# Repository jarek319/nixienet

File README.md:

# nixienet
Connecting 1960's tube tech to 2010's Wifi chips!

This Wifi gadget connects to time and weather forecast servers and uses Nixie tubes to display the current time and upcoming weather.

It's one of the most full designs I've ever made, from insides to outsides. So fun :)

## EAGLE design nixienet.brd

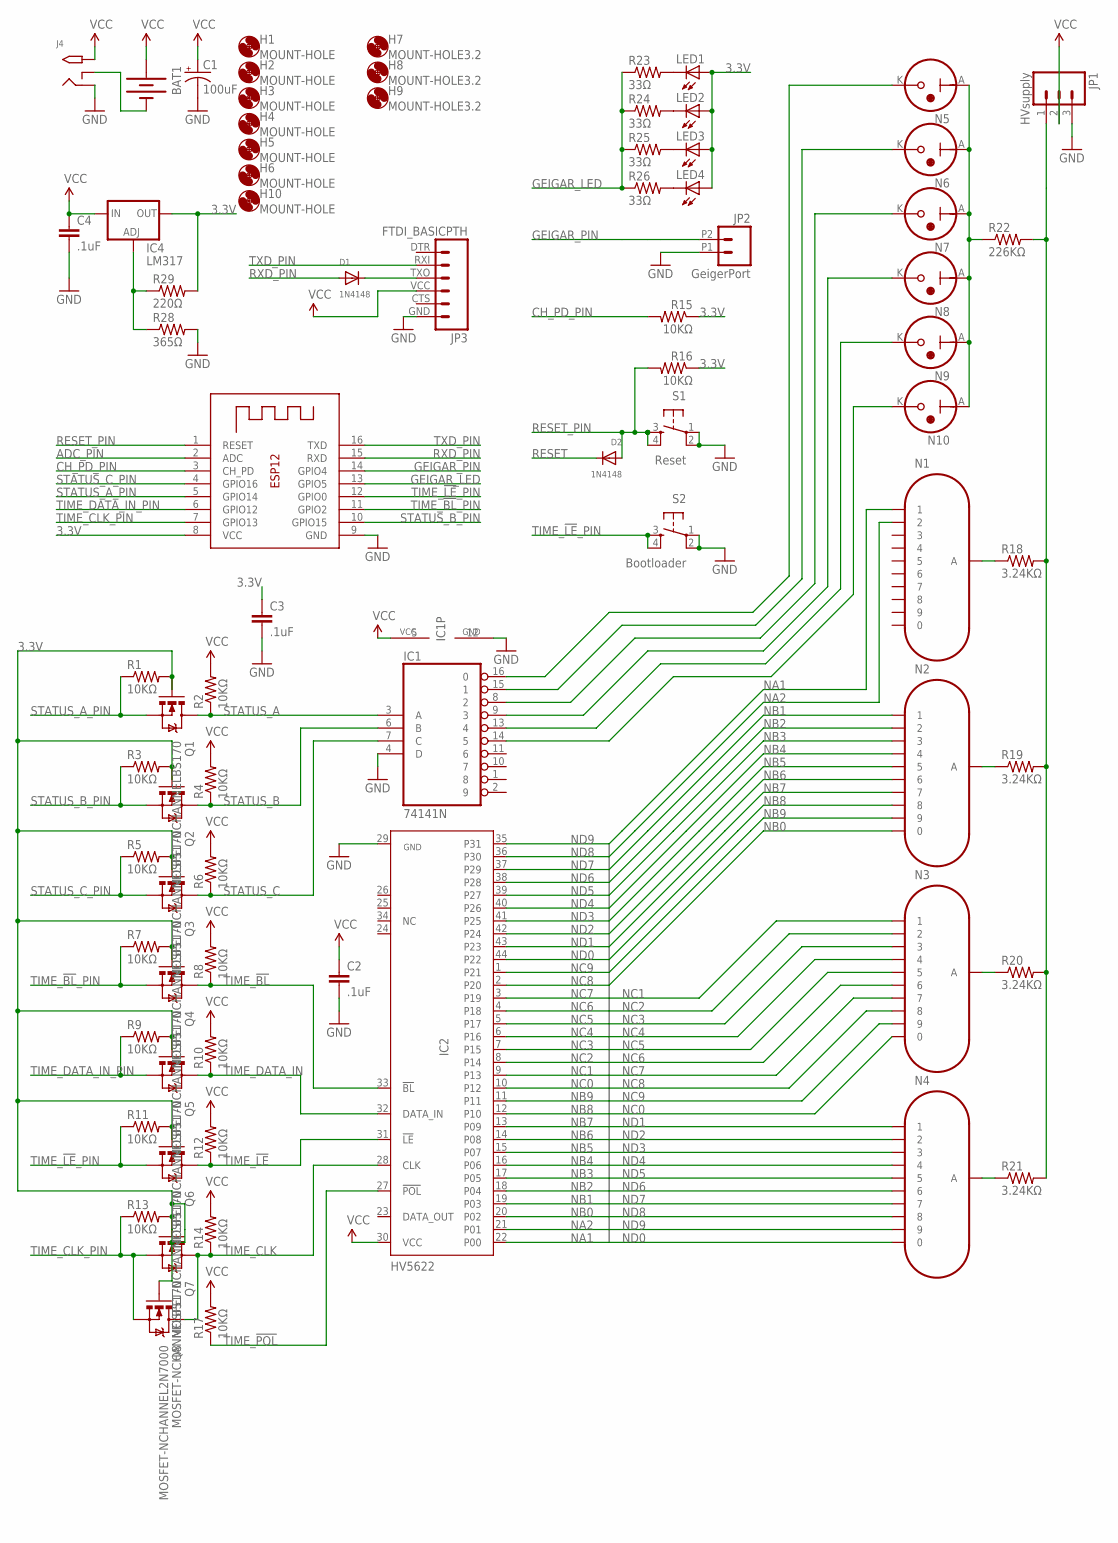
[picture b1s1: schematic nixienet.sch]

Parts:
BAT1: BATTERY9V; BATTCON_9V
C1: 100uF; E5-8,5
C2, C3, C4: .1uF; CAP-PTH-SMALLEZ
D1, D2: 1N4148
H1, H2, H3, H4, H5, H6, H10: MOUNT-HOLE; 3,2-DANGER
H7, H8, H9: MOUNT-HOLE3.2; 3,2
IC1: 74141N; DIL16
IC2: HV5622; QFP44
IC3: ESP-12
IC4: LM317; SPARKFUN-POWERIC_TO220-ADJ
J4: 2.1MMJACKTHM; PJ-102A
JP1: HVsupply; SCREWTERMINAL-5MM-3
JP2: GeigerPort; 1X02_2.54_SCREWTERM
JP3: FTDI_BASICPTH; FTDI_BASIC
LED1, LED2, LED3, LED4: LED5MM
N1: Hour1; IN-18
N2: Hour2; IN-18
N3: Minutes1; IN-18
N4: Minutes2; IN-18
N5: TopBulb; INS-1
N6: BottomBulb; INS-1
N7: SunnyBulb; INS-1
N8: CloudyBulb; INS-1
N9: RainyBulb; INS-1
N10: SnowyBulb; INS-1
Q1, Q2, Q3, Q4, Q5, Q6, Q7: MOSFET-NCHANNELBS170; TO-92
Q8: MOSFET-NCHANNEL2N7000; TO-92
R1, R2, R3, R4, R5, R6, R7, R8, R9, R10, R11, R12, R13, R14, R15, R16, R17: 10KΩ; 0204/5
R18, R19, R20, R21: 3.24KΩ; 0204/5
R22: 226KΩ; 0204/5
R23, R24, R25, R26: 33Ω; 0204/5
R28: 365Ω; 0204/5
R29: 220Ω; 0204/5
S1: Reset; TACTILE-PTH
S2: Bootloader; TACTILE-PTH

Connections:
3.3V: C3.1, IC3.8 (VCC), IC4.OUT, LED1.A, LED2.A, LED3.A, LED4.A, Q1.2 (G), Q2.2 (G), Q3.2 (G), Q4.2 (G), Q5.2 (G), Q6.2 (G), Q7.2 (G), Q8.2 (G), R1.2, R3.2, R5.2, R7.2, R9.2, R11.2, R13.2, R15.1, R16.1, R29.2
ADC_PIN: IC3.2 (ADC)
CH_PD_PIN: IC3.3 (CH_PD), R15.2
GEIGAR_LED: IC3.13 (GPIO5), R23.1, R24.1, R25.1, R26.1
GEIGAR_PIN: IC3.14 (GPIO4), JP2.P2 (2)
GND: C1.-, C2.2, C3.2, C4.2, IC1.4 (D), IC1.12 (GND), IC2.29 (GND), IC3.9 (GND), J4.RING, JP1.3, JP2.P1 (1), JP3.GND (6), R28.2, S1.1, S1.2, S2.1, S2.2
HV: JP1.1, R18.2, R19.2, R20.2, R21.2, R22.2
HV1: N1.4 (A), R18.1
HV2: N2.4 (A), R19.1
HV3: N3.4 (A), R20.1
HV4: N4.4 (A), R21.1
HVB: N5.A, N6.A, N7.A, N8.A, N9.A, N10.A, R22.1
unnamed: IC4.ADJ, R28.1, R29.1
unnamed: IC1.14 (5), N10.K
unnamed: IC1.13 (4), N9.K
unnamed: IC1.9 (3), N8.K
unnamed: IC1.8 (2), N7.K
unnamed: IC1.15 (1), N6.K
unnamed: IC1.16 (0), N5.K
unnamed: D1.K (C), JP3.TXO (3)
unnamed: BAT1.-, J4.RING_SW
unnamed: LED1.K (C), R23.2
unnamed: LED3.K (C), R25.2
unnamed: LED4.K (C), R26.2
unnamed: LED2.K (C), R24.2
NA1: IC2.22 (P00), N1.14 (1)
NA2: IC2.21 (P01), N1.9 (2)
NB0: IC2.20 (P02), N2.8 (0)
NB1: IC2.19 (P03), N2.14 (1)
NB2: IC2.18 (P04), N2.9 (2)
NB3: IC2.17 (P05), N2.11 (3)
NB4: IC2.16 (P06), N2.1 (4)
NB5: IC2.15 (P07), N2.12 (5)
NB6: IC2.14 (P08), N2.2 (6)
NB7: IC2.13 (P09), N2.6 (7)
NB8: IC2.12 (P10), N2.3 (8)
NB9: IC2.11, N2.5 (9)
NC0: IC2.10 (P12), N3.8 (0)
NC1: IC2.9 (P13), N3.14 (1)
NC2: IC2.8 (P14), N3.9 (2)
NC3: IC2.7 (P15), N3.11 (3)
NC4: IC2.6 (P16), N3.1 (4)
NC5: IC2.5 (P17), N3.12 (5)
NC6: IC2.4 (P18), N3.2 (6)
NC7: IC2.3 (P19), N3.6 (7)
NC8: IC2.2 (P20), N3.3 (8)
NC9: IC2.1 (P21), N3.5 (9)
ND0: IC2.44 (P22), N4.8 (0)
ND1: IC2.43 (P23), N4.14 (1)
ND2: IC2.42 (P24), N4.9 (2)
ND3: IC2.41 (P25), N4.11 (3)
ND4: IC2.40 (P26), N4.1 (4)
ND5: IC2.39 (P27), N4.12 (5)
ND6: IC2.38 (P28), N4.2 (6)
ND7: IC2.37 (P29), N4.6 (7)
ND8: IC2.36 (P30), N4.3 (8)
ND9: IC2.35 (P31), N4.5 (9)
RESET: D2.K (C)
RESET_PIN: D2.A, IC3.1 (RESET), R16.2, S1.3, S1.4
RXD_PIN: D1.A, IC3.15 (RXD)
STATUS_A: IC1.3 (A), Q1.1 (D), R2.1
STATUS_A_PIN: IC3.5 (GPIO14), Q1.3 (S), R1.1
STATUS_B: IC1.6 (B), Q2.1 (D), R4.1
STATUS_B_PIN: IC3.10 (GPIO15), Q2.3 (S), R3.1
STATUS_C: IC1.7 (C), Q3.1 (D), R6.1
STATUS_C_PIN: IC3.4 (GPIO16), Q3.3 (S), R5.1
TIME_!BL: IC2.33 (!BL), Q4.1 (D), R8.1
TIME_!BL!_PIN: IC3.11 (GPIO2), Q4.3 (S), R7.1
TIME_!LE: IC2.31 (!LE!), Q6.1 (D), R12.1
TIME_!LE!_PIN: IC3.12 (GPIO0), Q6.3 (S), R11.1, S2.3, S2.4
TIME_!POL: IC2.27 (!POL!), R17.1
TIME_CLK: IC2.28 (CLK), Q7.1 (D), Q8.3 (D), R14.1
TIME_CLK_PIN: IC3.7 (GPIO13), Q7.3 (S), Q8.1 (S), R13.1
TIME_DATA_IN: IC2.32 (DATA_IN), Q5.1 (D), R10.1
TIME_DATA_IN_PIN: IC3.6 (GPIO12), Q5.3 (S), R9.1
TXD_PIN: IC3.16 (TXD), JP3.RXI (2)
VCC: BAT1.+, C1.+, C2.1, C4.1, IC1.5 (VCC), IC2.30 (VCC), IC4.IN, J4.TIP, JP1.2, JP3.VCC (4), R2.2, R4.2, R6.2, R8.2, R10.2, R12.2, R14.2, R17.2

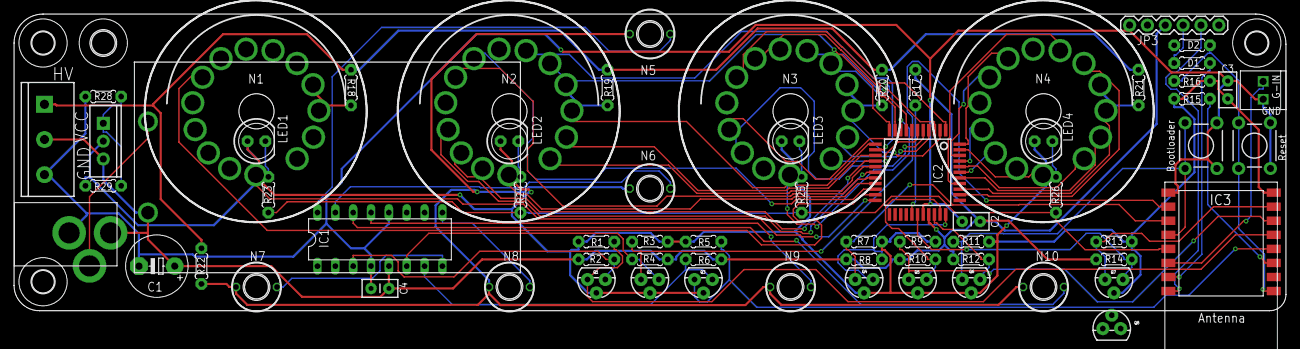
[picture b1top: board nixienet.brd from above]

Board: 2 copper layers, 181.0 x 42.2 mm, 77 parts (0 on the bottom side), 75 nets.

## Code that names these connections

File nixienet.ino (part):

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
int GEIGER_PIN = 5;
int GEIGER_LED = 4;
int TIME_DATA_IN_PIN = 12;
int TIME_CLK_PIN = 13;
int TIME_LE_PIN = 0;
int TIME_BL_PIN = 2;
int STATUS_A_PIN = 14;
int STATUS_B_PIN = 15;
int STATUS_C_PIN = 16;

struct nixieStruct {
  byte hour1;
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  }

  int c = 0;                            //initialize counter
  digitalWrite(TIME_LE_PIN, LOW);       //open shift register latch
  digitalWrite(TIME_DATA_IN_PIN, LOW);  //set next bit low
  for (c = 0; c < 32; c++) {            //push low bit 32 times to clear the register
    digitalWrite(TIME_CLK_PIN, HIGH);
    digitalWrite(TIME_CLK_PIN, LOW);
  }
  digitalWrite(TIME_LE_PIN, HIGH);      //push latch
  digitalWrite(TIME_LE_PIN, LOW);       //open latch
  digitalWrite(TIME_DATA_IN_PIN, LOW);  //set next bit low
  for (c = 9; c > nixies.minute2; c--) {
    digitalWrite(TIME_CLK_PIN, HIGH);
    digitalWrite(TIME_CLK_PIN, LOW);
  }
  digitalWrite(TIME_DATA_IN_PIN, HIGH);
  digitalWrite(TIME_CLK_PIN, HIGH);
  digitalWrite(TIME_CLK_PIN, LOW);
  digitalWrite(TIME_DATA_IN_PIN, LOW);
  for (c; c > 0; c--) {
    digitalWrite(TIME_CLK_PIN, HIGH);
    digitalWrite(TIME_CLK_PIN, LOW);
  }
  digitalWrite(TIME_DATA_IN_PIN, LOW);
  for (c = 9; c > nixies.minute1; c--) {
    digitalWrite(TIME_CLK_PIN, HIGH);
    digitalWrite(TIME_CLK_PIN, LOW);
  }
  digitalWrite(TIME_DATA_IN_PIN, HIGH);
  digitalWrite(TIME_CLK_PIN, HIGH);
  digitalWrite(TIME_CLK_PIN, LOW);
  digitalWrite(TIME_DATA_IN_PIN, LOW);
  for (c; c > 0; c--) {
    digitalWrite(TIME_CLK_PIN, HIGH);
    digitalWrite(TIME_CLK_PIN, LOW);
  }
  digitalWrite(TIME_DATA_IN_PIN, LOW);
  for (c = 9; c > nixies.hour2; c--) {
    digitalWrite(TIME_CLK_PIN, HIGH);
    digitalWrite(TIME_CLK_PIN, LOW);
  }
  digitalWrite(TIME_DATA_IN_PIN, HIGH);
  digitalWrite(TIME_CLK_PIN, HIGH);
  digitalWrite(TIME_CLK_PIN, LOW);
  digitalWrite(TIME_DATA_IN_PIN, LOW);
  for (c; c > 0; c--) {
    digitalWrite(TIME_CLK_PIN, HIGH);
    digitalWrite(TIME_CLK_PIN, LOW);
  }
  digitalWrite(TIME_DATA_IN_PIN, LOW);
  if (nixies.hour1 != 0) {
    for (c = 2; c > nixies.hour1; c--) {
      digitalWrite(TIME_CLK_PIN, HIGH);
      digitalWrite(TIME_CLK_PIN, LOW);
    }
    digitalWrite(TIME_DATA_IN_PIN, HIGH);
    digitalWrite(TIME_CLK_PIN, HIGH);
    digitalWrite(TIME_CLK_PIN, LOW);
    digitalWrite(TIME_DATA_IN_PIN, LOW);
    for (c; c > 1; c--) {
      digitalWrite(TIME_CLK_PIN, HIGH);
      digitalWrite(TIME_CLK_PIN, LOW);
    }
  }
  else {
    for (int i = 0; i < 2; i++) {
      digitalWrite(TIME_CLK_PIN, HIGH);
      digitalWrite(TIME_CLK_PIN, LOW);
    }
  }
  digitalWrite(TIME_LE_PIN, HIGH);

  if (nixies.bulbs & 0x01) { // Top Colon
    digitalWrite(STATUS_A_PIN, LOW);
    digitalWrite(STATUS_B_PIN, LOW);
    digitalWrite(STATUS_C_PIN, LOW);
    delayMicroseconds(nixieBulbDelayTime);
  }
  if (nixies.bulbs & 0x02) { // Botton Colon
    digitalWrite(STATUS_A_PIN, HIGH);
    digitalWrite(STATUS_B_PIN, LOW);
    digitalWrite(STATUS_C_PIN, LOW);
    delayMicroseconds(nixieBulbDelayTime);
  }
  if (nixies.bulbs & 0x04) { // Sun
    digitalWrite(STATUS_A_PIN, LOW);
    digitalWrite(STATUS_B_PIN, HIGH);
    digitalWrite(STATUS_C_PIN, HIGH);
    delayMicroseconds(nixieBulbDelayTime);
  }
  if (nixies.bulbs & 0x08) { // Cloud
    digitalWrite(STATUS_A_PIN, LOW);
    digitalWrite(STATUS_B_PIN, HIGH);
    digitalWrite(STATUS_C_PIN, LOW);
    delayMicroseconds(nixieBulbDelayTime);
  }
  if (nixies.bulbs & 0x10) { // Rain
    digitalWrite(STATUS_A_PIN, LOW);
    digitalWrite(STATUS_B_PIN, LOW);
    digitalWrite(STATUS_C_PIN, HIGH);
    delayMicroseconds(nixieBulbDelayTime);
  }
  if (nixies.bulbs & 0x20) { // Snow
    digitalWrite(STATUS_A_PIN, HIGH);
    digitalWrite(STATUS_B_PIN, LOW);
    digitalWrite(STATUS_C_PIN, HIGH);
    delayMicroseconds(nixieBulbDelayTime);
  }
}
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  pinMode(GEIGER_PIN, INPUT);
  pinMode(GEIGER_LED, OUTPUT);
  digitalWrite(GEIGER_LED, LOW);
  pinMode(TIME_DATA_IN_PIN, OUTPUT);
  digitalWrite(TIME_DATA_IN_PIN, LOW);
  pinMode(TIME_CLK_PIN, OUTPUT);
  digitalWrite(TIME_CLK_PIN, LOW);
  pinMode(TIME_LE_PIN, OUTPUT);
  digitalWrite(TIME_LE_PIN, HIGH);
  pinMode(TIME_BL_PIN, OUTPUT);
  digitalWrite(TIME_BL_PIN, HIGH);
  pinMode(STATUS_A_PIN, OUTPUT);
  digitalWrite(STATUS_A_PIN, HIGH);
  pinMode(STATUS_B_PIN, OUTPUT);
  digitalWrite(STATUS_B_PIN, HIGH);
  pinMode(STATUS_C_PIN, OUTPUT);
  digitalWrite(STATUS_C_PIN, HIGH);
  drawNixies();

  Serial.begin(115200);
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
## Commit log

2018-07-05 design tested: working
2018-07-05 adding pictures

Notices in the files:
parts and their libraries:
SparkFun-Connectors: Licensing: CC v3.0 Share-Alike You are welcome to use this library for commercial purposes.
